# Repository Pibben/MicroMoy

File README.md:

# MicroMoy

## Prototype
### Power supply
* https://tangentsoft.net/elec/vgrounds.html
* Input jack 5.5x2.5mm (11x9x14mm)
  * https://www.tme.eu/en/details/1613-15/dc-power-connectors/lumberg/1613-15/# 13kr
  
* Virtual Ground IC
  * http://www.ti.com/lit/ds/symlink/buf634.pdf
    * https://www.mouser.se/ProductDetail/Texas-Instruments/BUF634U-2K5?qs=sGAEpiMZZMsko7UDAsUSIRkNM9cw4BxWuQR3Y9PwaQU%3d 8€
    * https://www.ebay.com/itm/BUF634U-IC-SOIC8-OP-AMP-BURR-BROWN/153064931267 69+30kr
  * http://www.ti.com/lit/gpn/lmh6321
    * https://www.mouser.se/ProductDetail/Texas-Instruments/LMH6321MR-NOPB?qs=sGAEpiMZZMtCHixnSjNA6M%252bbBaCn4IWbwBZuS4vckcA%3d 5€
* Cap 35V
  * https://www.tme.eu/en/details/eeefk1v331p/smd-low-imp-electrolytic-capacitors/panasonic/ 330uF 3kr
  * https://www.mouser.se/ProductDetail/United-Chemi-Con/EMZS350ARA471MHA0G?qs=sGAEpiMZZMtZ1n0r9vR22cpFQt4dfSbqKMnuCzUTFvUCJYhxMu30Jg%3d%3d 470uF 0.7€
* 2 220k resistors

### Volume control alternative 1
* Rotary encoder
  * https://www.tme.eu/en/Document/0ebbc64ade625a62b285b77e718a2ac7/ALPS-EC11J.pdf 15x18mm (11x14) O=9mm @ 4.5mm.
    * https://www.tme.eu/en/details/ec11j1524413/incremental-type-encoders/alps/ 15kr
    * https://www.ebay.com/itm/EC11J1524413-Encoder-incremental-Mounting-SMD-SMT-15imp-revol-10mA-ALPS/401475259406 47+11kr
    * https://www.mouser.se/ProductDetail/ALPS/EC11J1524413?qs=%2fha2pyFaduh7AImzMyKctVfqHwIT8vYmn%252b1rkWaisnXlIU1aABuDkQ%3d%3d 4.67€
* Volume control IC
  * https://datasheets.maximintegrated.com/en/ds/MAX5440.pdf
    * https://www.ebay.com/sch/i.html?_from=R40&_nkw=MAX5440&_sacat=0&_sop=15 25+35kr
    * https://www.mouser.se/ProductDetail/Maxim-Integrated/MAX5440EAG%2b?qs=%2fha2pyFaduj%252bUuifj%252bX18AtYLH0Zs5TS%252byLsRIch5DQ%3d 1.50€
* 5V coltage converter

### Volume control alternative 2
* Potentiometer (9x9x16mm)
* Voltage-controlled resistor FET

### Amplifier
* Dual OpAmp IC (SOIC-8) (OPA2132, AD826, OPA2604, LT1364, AD823, AD8620, OPA2134, OPA227) DIL-8, 10x10x3mm
* DIL socket
  * https://www.tme.eu/en/details/gold-8p-smd/precision-sockets/connfly/ds1001-02-08n13/ 5.33mm 6kr
  * https://www.mouser.se/ProductDetail/Mill-Max/110-47-308-41-105000?qs=sGAEpiMZZMs%2fSh%2fkjph1tkCPjfxlAKUmMb0760r1HTQ%3d 1€
* 0.1 uF caps (0.22 µF, 0.47 µF)
* In- / Output jacks
  * https://www.tme.eu/en/details/1503-02/jack-connectors/lumberg/1503-02/ 5x6x19mm 11kr
  
### Board-to-board
* https://www.tme.eu/en/details/ph1-40-ua-smt-a/pin-headers/adam-tech/ 3+6mm
* https://www.tme.eu/en/details/ph2-80-ua-smt/pin-headers/adam-tech/ 3+6mm
* https://www.tme.eu/en/details/ds1002-01-1x60s13/pin-headers/connfly/ds1002-01-1_60s13/ 2.6+3mm (female)
* https://www.tme.eu/en/details/zl264-4dg/pin-headers/ninigi/ 7mm

## References

* https://datasheets.maximintegrated.com/en/ds/DS1802.pdf
* https://download.siliconexpert.com/pdfs/2015/12/18/16/4/11/191/lsicsi_/manual/3ls7083_ls7084.pdf
* https://www.maximintegrated.com/en/products/analog/data-converters/digital-potentiometers/MAX5440.html
* https://eu.mouser.com/datasheet/2/15/EC11-1370822.pdf
* https://4donline.ihs.com/images/VipMasterIC/IC/SILX/SILXS13275/SILXS13275-1.pdf
* http://www.circuitdiagramworld.com/led_circuit_diagram/Voltage_Controlled_Attenuator__Volume_Control__Using_FET_17666.html
* https://www.diystompboxes.com/smfforum/index.php?topic=94466.0
* http://www.calogic.net/pdf/SST404_Datasheet_Rev_A.pdf
* http://www.onsemi.com/pub/Collateral/ENA1966-D.PDF
* http://www.farnell.com/datasheets/1815497.pdf PMBFJ620
* https://www.vishay.com/docs/70598/70598.pdf
* https://www.tme.eu/en/Document/61a0705501a0f89f07f25672e998ba0b/ALPS_RK097.pdf
* https://www.mouser.se/datasheet/2/414/Datasheet_PanelPot_P09xSeries-1134489.pdf
* https://www.mouser.se/datasheet/2/54/tr90-777814.pdf

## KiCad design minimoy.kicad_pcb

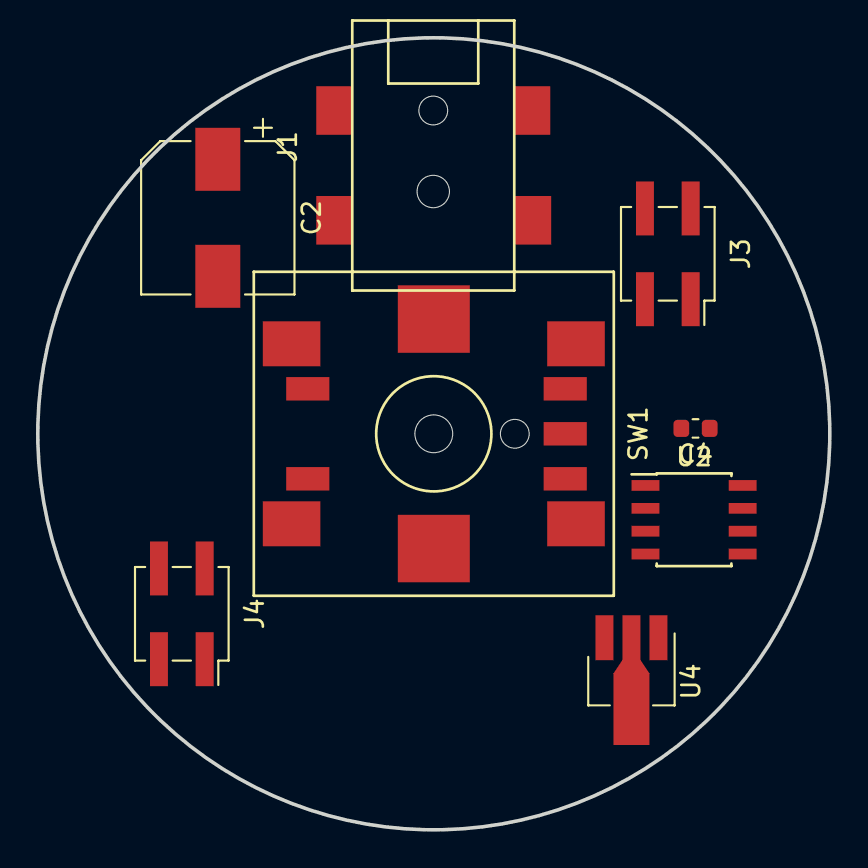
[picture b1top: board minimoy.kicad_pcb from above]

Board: 2 copper layers, 44.0 x 44.0 mm, 8 parts (0 on the bottom side), 7 nets, no tracks yet.

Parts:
C2: 330uF; CP_Elec_8x10
C4: 1 uF; C_0603_1608Metric
J1: Barrel_Jack; BARREL_CON_SMD
J3, J4: Conn_02x02_Odd_Even; PinSocket_2x02_P2.54mm_Vertical_SMD
SW1: Rotary_Encoder; ALPS_EC11_SMD
U2: TLE2426xD; SOIC-8_3.9x4.9mm_P1.27mm
U4: L7805; SOT-89-3_Handsoldering

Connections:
+24V: C2.1, J1.1, J4.2, U2.3, U4.1
/-12V_LOWER: C2.2, C4.2, J1.2, J4.4, U2.2
/VGND_LOWER: J3.2, J3.4, J4.3, SW1.C, U2.1, U4.2
unnamed: C4.1, U2.8
unnamed: J3.1, SW1.A
unnamed: J3.3, SW1.B
unnamed: J4.1, U4.3

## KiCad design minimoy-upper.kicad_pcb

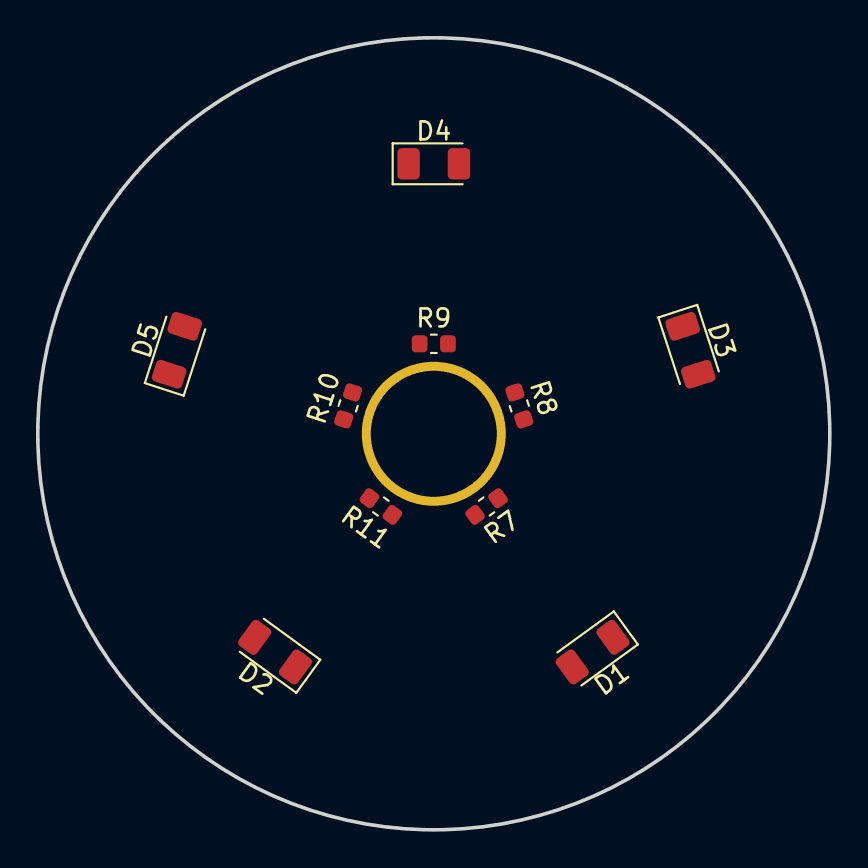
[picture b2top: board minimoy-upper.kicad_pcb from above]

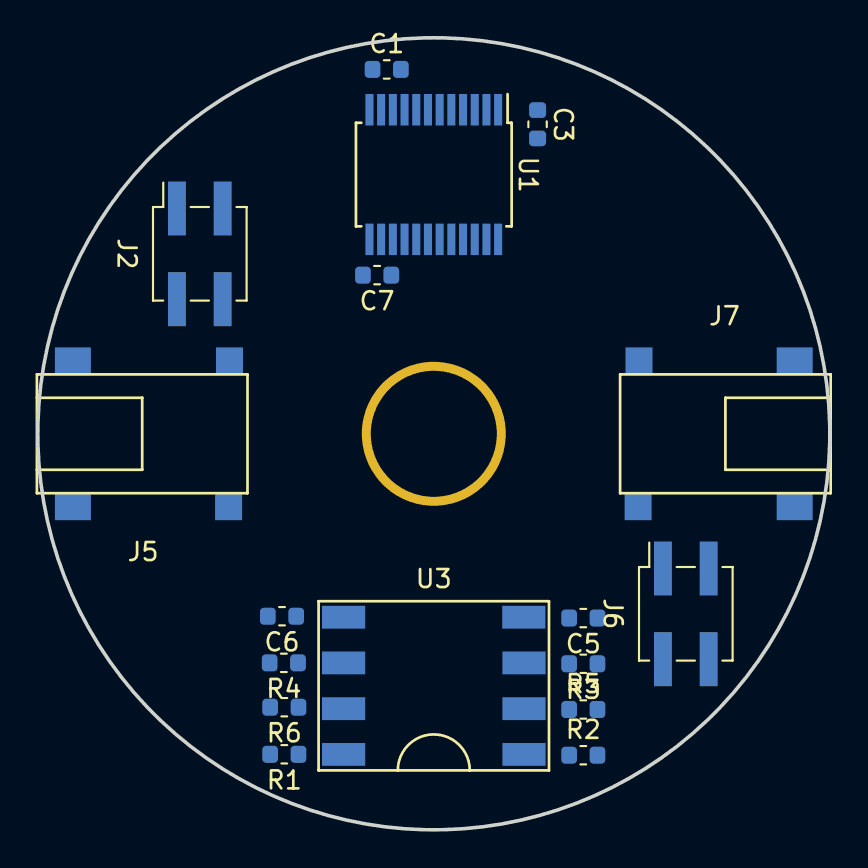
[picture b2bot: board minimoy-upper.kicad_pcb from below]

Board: 2 copper layers, 44.0 x 44.0 mm, 27 parts (17 on the bottom side), 29 nets, no tracks yet.

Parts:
C1, C3, C7: 0.1uF; C_0603_1608Metric
C5, C6: 0.22uF; C_0603_1608Metric
D1, D2, D3, D4, D5: LED; LED_1206_3216Metric
J2, J6: Conn_02x02_Odd_Even; PinSocket_2x02_P2.54mm_Vertical_SMD
J5, J7: AudioJack3_Ground; STEREO_JACK_SMD
R1, R2: 10k; R_0603_1608Metric
R3, R4: 100k; R_0603_1608Metric
R5, R6: 1k; R_0603_1608Metric
R7, R8, R9, R10, R11: 680; R_0603_1608Metric
U1: MAX5440EAG; SSOP-24_5.3x8.2mm_P0.65mm
U3: OPA2134; DIL_8_SMD

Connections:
/5V_UPPER: C7.2, U1.13
/+5V_UPPER: C3.1, J6.2, U1.1
/+12V_UPPER: J6.1, R7.1, R8.1, R9.1, R10.1, R11.1, U3.8
/-12V_UPPER: J6.3, U3.4
/GND_UPPER: C3.2, J7.S
/LEFT: C5.2, U1.10
/LEFT_IN: J7.T, U1.8
/RIGHT: C6.2, U1.15
/RIGHT_IN: J7.R, U1.17
/VGND_UPPER: C1.2, C7.1, J2.1, J2.3, J5.S, J6.4, R3.2, R4.2, R5.2, R6.2, U1.7, U1.9, U1.14, U1.16, U1.24
unnamed: C1.1, U1.12
unnamed: C5.1, R3.1, U3.3
unnamed: C6.1, R4.1, U3.5
unnamed: D1.1, U1.22
unnamed: D1.2, R7.2
unnamed: D2.1, U1.18
unnamed: D2.2, R11.2
unnamed: D3.1, U1.21
unnamed: D3.2, R8.2
unnamed: D4.1, U1.20
unnamed: D4.2, R9.2
unnamed: D5.1, U1.19
unnamed: D5.2, R10.2
unnamed: J2.2, U1.2
unnamed: J2.4, U1.3
unnamed: J5.R, R1.1, U3.7
unnamed: J5.T, R2.1, U3.1
unnamed: R1.2, R6.1, U3.6
unnamed: R2.2, R5.1, U3.2

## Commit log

2018-09-19 First commit.
2018-09-29 Placed upper board.
2018-09-29 Move 7805 to lower board. Make room for cap on upper board.
2018-10-30 Fix DC jack footprint.
2018-10-30 Update schematic.
2018-10-30 Larger PCB.
